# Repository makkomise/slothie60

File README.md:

# Slothie60

## 60% ISO/ANSI keyboard

- GH60-Compatible
- Underglow
- QMK/VIAL compatible

## Supports:
  - ISO or ANSI-layout
  - 1.25U or 2.25U Left Shift
  - 1.75U or 2.75U Right Shift
  - 6.25U or 2.75U/1.25U/2.25U Space bar 

ORDERING AT YOUR OWN RESPONSIBILITY! While i have confirmed that this works, order at your own discretion.

Version 2a is a work in progress, 1b is the finished one so if you want to get one, pick that.
KiCad folder includes all the project files, feel free to modify to your own liking. 
Production folder includes all the needed files for ordering these. Zip has all the gerbers, BOM and POS files are needed if you order it assembled.
Firmware-folder has all the files needed for you to either modify and compile yourself, or you can just download the binary and flash it in QMK Toolbox.

Keyboard made under CERN-OHL-W v2 license.

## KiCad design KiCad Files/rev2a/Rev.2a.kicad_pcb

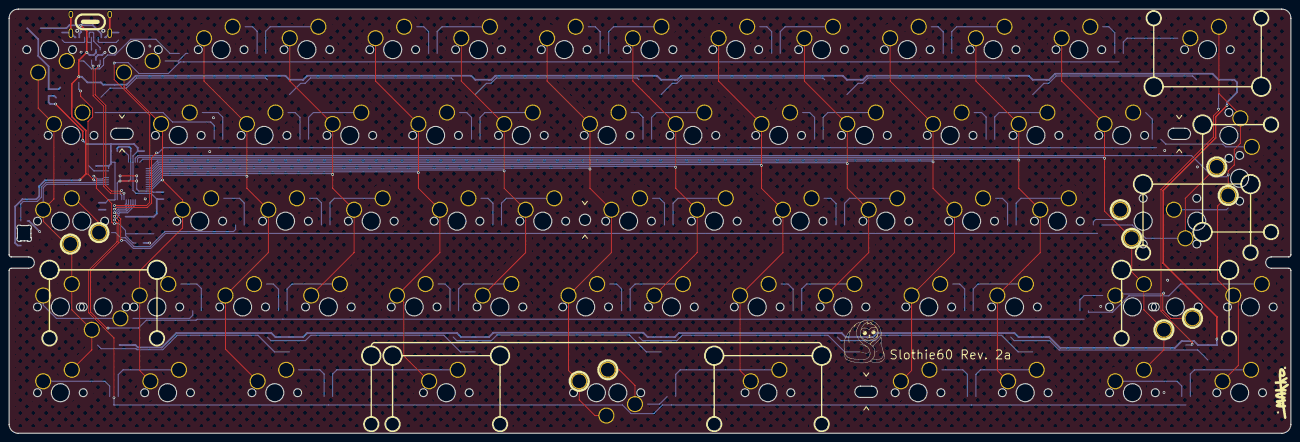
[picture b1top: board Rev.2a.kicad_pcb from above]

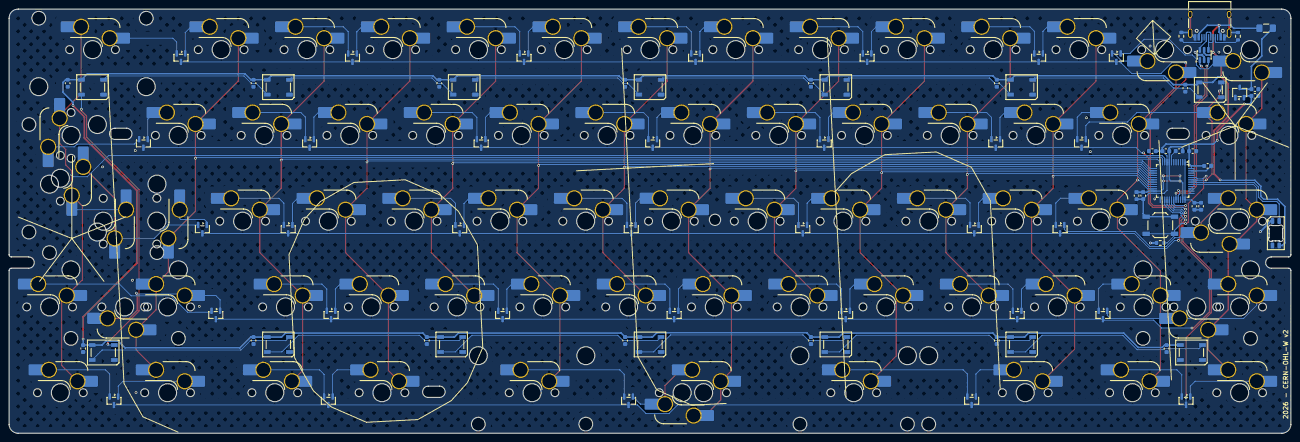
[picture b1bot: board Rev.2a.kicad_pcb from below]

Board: 2 copper layers, 284.6 x 94.1 mm, 161 parts (82 on the bottom side), 112 nets.

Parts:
BOOTSW1: SW_Push; SW_SPST_TL3342
BOOT_R1: 10k; R_0603_1608Metric
C1, C2, C3, C4, C5, C6, C7, C8, C9, C10, C11, C12, C13, C14: 100nF; C_0603_1608Metric
CLED1: SK6812MINI-E; LED_SK6812MINI-E_3.2x2.8mm_P1.5mm_ReverseMount
D1, D2, D3, D4, D5, D6, D7, D8, D9, D10, D11, D12, D13, D14, D15, D16, D17, D18, D19, D20, D21, D22, D23, D24, D25, D26, D27, D28, D29, D30, D31, D32, D33: BAV70; SOT-23
ESD1: USBLC6-2SC6; SOT-23-6
F1: 500mA; Fuse_1206_3216Metric_Pad1.42x1.75mm_HandSolder
LED1, LED2, LED3, LED4, LED5, LED6, LED7, LED8, LED9, LED10, LED11, LED12, LED13, LED14: WS2812C; LED_WS2812B_PLCC4_5.0x5.0mm_P3.2mm
MCU1: STM32F072CBT6; LQFP-48_7x7mm_P0.5mm
MCU_C1, MCU_C2, MCU_C3, MCU_C5, MCU_C8: 100nF; C_0603_1608Metric
MCU_C4, MCU_C9: 4.7uF; C_0603_1608Metric
MCU_C6: 10nF; C_0603_1608Metric
MCU_C7: 1uF; C_0603_1608Metric
REG1: XC6206; SOT-23-3
REG_C1, REG_C2: 1uF; C_0603_1608Metric
S1, S2, S3, S4, S5, S6, S7: Stabilizer_2U; Stabilizer_Cherry_MX_2.00u
S8: Stabilizer_6.25U; Stabilizer_Cherry_MX_6.25u
SW1, SW2, SW3, SW4, SW5, SW6, SW7, SW8, SW9, SW10, SW11, SW12, SW13, SW14, SW15, SW16, SW17, SW18, SW19, SW20, SW21, SW22, SW23, SW24, SW25, SW26, SW27, SW31, SW32, SW33, SW34, SW35, SW36, SW37, SW38, SW39, SW40, SW41, SW42, SW47, SW48, SW49, SW50, SW51, SW52, SW53, SW54, SW55, SW56, SW57, SW60: SW_Hotswap_Kailh_MX_Plated_1.00u_NoBorder
SW28: SW_Hotswap_Kailh_MX_Plated_1.50u_90deg
SW29, SW46, SW61, SW62, SW63, SW66, SW68, SW69, SW70, SW71: SW_Hotswap_Kailh_MX_Plated_1.25u
SW30, SW58: SW_Hotswap_Kailh_MX_Plated_1.75u
SW43: SW_Hotswap_Kailh_MX_Plated_2.25u_90deg
SW44: SW_Hotswap_Kailh_MX_Plated_ISOEnter_90deg
SW45, SW67: SW_Hotswap_Kailh_MX_Plated_2.25u
SW59, SW64: SW_Hotswap_Kailh_MX_Plated_2.75u
SW65: SW_Hotswap_Kailh_MX_Plated_6.25u
USB1: USB_C; USB_C_Receptacle_HRO_TYPE-C-31-M-12
USB_R1, USB_R2: 5.1k; R_0603_1608Metric

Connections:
+3.3V: BOOTSW1.1, MCU1.1 (VBAT), MCU1.9 (VDDA), MCU1.24 (VDD), MCU1.36 (VDDIO2), MCU1.48 (VDD), MCU_C2.2, MCU_C3.2, MCU_C4.2, MCU_C5.2, MCU_C6.2, MCU_C7.2, MCU_C8.2, MCU_C9.2, REG1.2 (VO), REG_C2.1
+5V: F1.2, REG1.3 (VI), REG_C1.1
/BOOT0: BOOTSW1.2, BOOT_R1.1, MCU1.44 (BOOT0)
/MCU_D+: ESD1.1 (I/O1), MCU1.33 (PA12)
/MCU_D-: ESD1.3 (I/O2), MCU1.32 (PA11)
/NRST: MCU1.7 (NRST), MCU_C1.1
/USB_D+: ESD1.6 (I/O1), USB1.A6 (D+), USB1.B6 (D+)
/USB_D-: ESD1.4 (I/O2), USB1.A7 (D-), USB1.B7 (D-)
BackLight: LED1.4 (DIN), MCU1.43 (PB7)
CapsLed: CLED1.2 (DIN), MCU1.42 (PB6)
Col0: MCU1.41 (PB5), SW1.2, SW15.1, SW29.1, SW30.2, SW45.2, SW46.2, SW61.2
Col1: MCU1.22 (PB11), SW2.2, SW16.1, SW31.1, SW47.1, SW62.1
Col2: MCU1.21 (PB10), SW3.1, SW17.1, SW32.1, SW48.1, SW63.1
Col3: MCU1.20 (PB2), SW4.1, SW18.1, SW33.1, SW49.1
Col4: MCU1.19 (PB1), SW5.1, SW19.1, SW34.1, SW50.1, SW64.1
Col5: MCU1.18 (PB0), SW6.1, SW20.1, SW35.1, SW51.1
Col6: MCU1.17 (PA7), SW7.1, SW21.1, SW36.1, SW52.1, SW65.1, SW66.2
Col7: MCU1.16 (PA6), SW8.1, SW22.1, SW37.1, SW53.1
Col8: MCU1.15 (PA5), SW9.1, SW23.1, SW38.1, SW54.1, SW67.1
Col9: MCU1.14 (PA4), SW10.1, SW24.1, SW39.1, SW55.1
Col10: MCU1.13 (PA3), SW11.1, SW25.1, SW40.1, SW56.1, SW68.1
Col11: MCU1.12 (PA2), SW12.1, SW26.1, SW41.1, SW57.1, SW69.1
Col12: MCU1.11 (PA1), SW13.1, SW27.1, SW42.1, SW58.2, SW59.2, SW70.2
Col13: MCU1.10 (PA0), SW14.2, SW28.1, SW43.2, SW44.1, SW60.1, SW71.1
GND: BOOT_R1.2, C1.2, C2.2, C3.2, C4.2, C5.2, C6.2, C7.2, C8.2, C9.2, C10.2, C11.2, C12.2, C13.2, C14.2, CLED1.1 (VSS), ESD1.2 (GND), LED1.3 (VSS), LED2.3 (VSS), LED3.3 (VSS), LED4.3 (VSS), LED5.3 (VSS), LED6.3 (VSS), LED7.3 (VSS), LED8.3 (VSS), LED9.3 (VSS), LED10.3 (VSS), LED11.3 (VSS), LED12.3 (VSS), LED13.3 (VSS), LED14.3 (VSS), MCU1.8 (VSSA), MCU1.23 (VSS), MCU1.35 (VSS), MCU1.47 (VSS), MCU_C1.2, MCU_C2.1, MCU_C3.1, MCU_C4.1, MCU_C5.1, MCU_C6.1, MCU_C7.1, MCU_C8.1, MCU_C9.1, REG1.1 (GND), REG_C1.2, REG_C2.2, USB1.A1 (GND), USB1.A12 (GND), USB1.B1 (GND), USB1.B12 (GND), USB1.S1 (SHIELD), USB_R1.2, USB_R2.2
unnamed: D1.1 (A), SW1.1
unnamed: D1.2 (A), SW2.1
unnamed: D2.1 (A), SW3.2
unnamed: D2.2 (A), SW4.2
unnamed: D3.1 (A), SW5.2
unnamed: D3.2 (A), SW6.2
unnamed: D4.1 (A), SW7.2
unnamed: D4.2 (A), SW8.2
unnamed: D5.1 (A), SW9.2
unnamed: D5.2 (A), SW10.2
unnamed: D6.1 (A), SW11.2
unnamed: D6.2 (A), SW12.2
unnamed: D7.1 (A), SW13.2
unnamed: D7.2 (A), SW14.1
unnamed: D8.1 (A), SW15.2
unnamed: D8.2 (A), SW16.2
unnamed: D9.1 (A), SW17.2
unnamed: D9.2 (A), SW18.2
unnamed: D10.1 (A), SW19.2
unnamed: D10.2 (A), SW20.2
unnamed: D11.1 (A), SW21.2
unnamed: D11.2 (A), SW22.2
unnamed: D12.1 (A), SW23.2
unnamed: D12.2 (A), SW24.2
unnamed: D13.1 (A), SW25.2
unnamed: D13.2 (A), SW26.2
unnamed: D14.1 (A), SW27.2
unnamed: D14.2 (A), SW28.2
unnamed: D15.1 (A), SW29.2, SW30.1
unnamed: D15.2 (A), SW31.2
unnamed: D16.1 (A), SW32.2
unnamed: D16.2 (A), SW33.2
unnamed: D17.1 (A), SW34.2
unnamed: D17.2 (A), SW35.2
unnamed: D18.1 (A), SW36.2
unnamed: D18.2 (A), SW37.2
unnamed: D19.1 (A), SW38.2
unnamed: D19.2 (A), SW39.2
unnamed: D20.1 (A), SW40.2
unnamed: D20.2 (A), SW41.2
unnamed: D21.1 (A), SW42.2
unnamed: D21.2 (A), SW43.1, SW44.2
unnamed: D22.1 (A), SW45.1, SW46.1
unnamed: D22.2 (A), SW47.2
unnamed: D23.1 (A), SW48.2
unnamed: D23.2 (A), SW49.2
unnamed: D24.1 (A), SW50.2
unnamed: D24.2 (A), SW51.2
unnamed: D25.1 (A), SW52.2
unnamed: D25.2 (A), SW53.2
unnamed: D26.1 (A), SW54.2
unnamed: D26.2 (A), SW55.2
unnamed: D27.1 (A), SW56.2
unnamed: D27.2 (A), SW57.2
unnamed: D28.1 (A), SW58.1, SW59.1
unnamed: D28.2 (A), SW60.2
unnamed: D29.1 (A), SW61.1
unnamed: D29.2 (A), SW62.2
unnamed: D30.1 (A), SW63.2
unnamed: D30.2 (A), SW64.2
unnamed: D31.1 (A), SW65.2, SW66.1
unnamed: D31.2 (A), SW67.2
unnamed: D32.1 (A), SW68.2
unnamed: D32.2 (A), SW69.2
unnamed: D33.1 (A), SW70.1
unnamed: D33.2 (A), SW71.2
unnamed: LED1.2 (DOUT), LED2.4 (DIN)
unnamed: LED2.2 (DOUT), LED3.4 (DIN)
unnamed: LED3.2 (DOUT), LED4.4 (DIN)
unnamed: LED4.2 (DOUT), LED5.4 (DIN)
unnamed: LED5.2 (DOUT), LED6.4 (DIN)
unnamed: LED6.2 (DOUT), LED7.4 (DIN)
unnamed: LED7.2 (DOUT), LED8.4 (DIN)
unnamed: LED8.2 (DOUT), LED9.4 (DIN)
unnamed: LED9.2 (DOUT), LED10.4 (DIN)
unnamed: LED10.2 (DOUT), LED11.4 (DIN)
unnamed: LED11.2 (DOUT), LED12.4 (DIN)
unnamed: LED12.2 (DOUT), LED13.4 (DIN)
unnamed: LED13.2 (DOUT), LED14.4 (DIN)
unnamed: USB1.A5 (CC1), USB_R1.1
unnamed: USB1.B5 (CC2), USB_R2.1
Row0: D1.3 (K), D2.3 (K), D3.3 (K), D4.3 (K), D5.3 (K), D6.3 (K), D7.3 (K), MCU1.31 (PA10)
Row1: D8.3 (K), D9.3 (K), D10.3 (K), D11.3 (K), D12.3 (K), D13.3 (K), D14.3 (K), MCU1.30 (PA9)
Row2: D15.3 (K), D16.3 (K), D17.3 (K), D18.3 (K), D19.3 (K), D20.3 (K), D21.3 (K), MCU1.29 (PA8)
Row3: D22.3 (K), D23.3 (K), D24.3 (K), D25.3 (K), D26.3 (K), D27.3 (K), D28.3 (K), MCU1.28 (PB15)
Row4: D29.3 (K), D30.3 (K), D31.3 (K), D32.3 (K), D33.3 (K), MCU1.27 (PB14)
VBUS: C1.1, C2.1, C3.1, C4.1, C5.1, C6.1, C7.1, C8.1, C9.1, C10.1, C11.1, C12.1, C13.1, C14.1, CLED1.3 (VDD), ESD1.5 (VBUS), F1.1, LED1.1 (VDD), LED2.1 (VDD), LED3.1 (VDD), LED4.1 (VDD), LED5.1 (VDD), LED6.1 (VDD), LED7.1 (VDD), LED8.1 (VDD), LED9.1 (VDD), LED10.1 (VDD), LED11.1 (VDD), LED12.1 (VDD), LED13.1 (VDD), LED14.1 (VDD), USB1.A4 (VBUS), USB1.A9 (VBUS), USB1.B4 (VBUS), USB1.B9 (VBUS)

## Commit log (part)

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2025-02-19 First commit
    - Added KiCad files
    - Added Production files for ordering
    - Added first version of firmware
    - Edited readme
2025-02-19 Updoot to firmware
    - added support for multiple layouts
2025-02-19 Update README.md
    Added picture of layouts
2025-02-19 updoot
2025-02-19 Fixed keyboard.json
    - Lint issues fixed, now everything (should) work
    - Removed unnecessary files.
2025-02-19 - Fixed keymap.c
    - Both custom keymaps had name wrong, fixed that
2025-02-19 Fixed .json and removed unnecessary files
2025-03-13 Update
    KiCad files had one small error, fixed it now
2025-03-14 updated firmware
    - added sleep function so lights go out when shutting down pc
2025-04-10 Updated to 1b
    - Removed split space
    - Updated led count and the pin
    - Updated firmware
2025-04-10 Update to revision 1b
    - Removed split space
    - Updated to 16 5050-leds
    - Changed to round routing
    - Updated firmware
    - Updated production and KiCad-folders to 9.0.1
2026-02-18 New revision
    - Moved 1b to it's own folder
    - Added folder 1c with base files to KiCad files (WIP, DO NOT USE)
2026-02-18 Rev1c preliminarty update
    Changes to Schematic:
    - Added switches to support different layouts
    - Added One BAV70 to support said switches
    Changes to PCB:
    - Imported changes from schematic, placed some of the switches but needs more work
2026-02-18 update on pcb
2026-02-21 FR4 Plate
    Plate done
2026-03-10 Plate stuff
    - Added a plate design for rev 1b
    - Some updates to 1c

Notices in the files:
KiCad Files/rev2a/Rev.2a.kicad_pcb:
2026 - CERN-OHL-W v2
